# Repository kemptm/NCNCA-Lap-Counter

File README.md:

# NCNCA-Lap-Counter
This is an electronic lap counter for use at the finish line of bike (or other) races.  It has two 9" solenoid activated 7-segment digits. It is run by an Arduino controlled by a little remote control with buttons "A," "B," "C," and "D."   It has a solar panel to charge the batteries, but apparently can be powered by an external power supply. 

Mike's son built it as a college project.  There is no documentation.  It's not new, so some of the parts are obsolete.  If I can get it operational, Mike intends to donate it to the NCNCA.

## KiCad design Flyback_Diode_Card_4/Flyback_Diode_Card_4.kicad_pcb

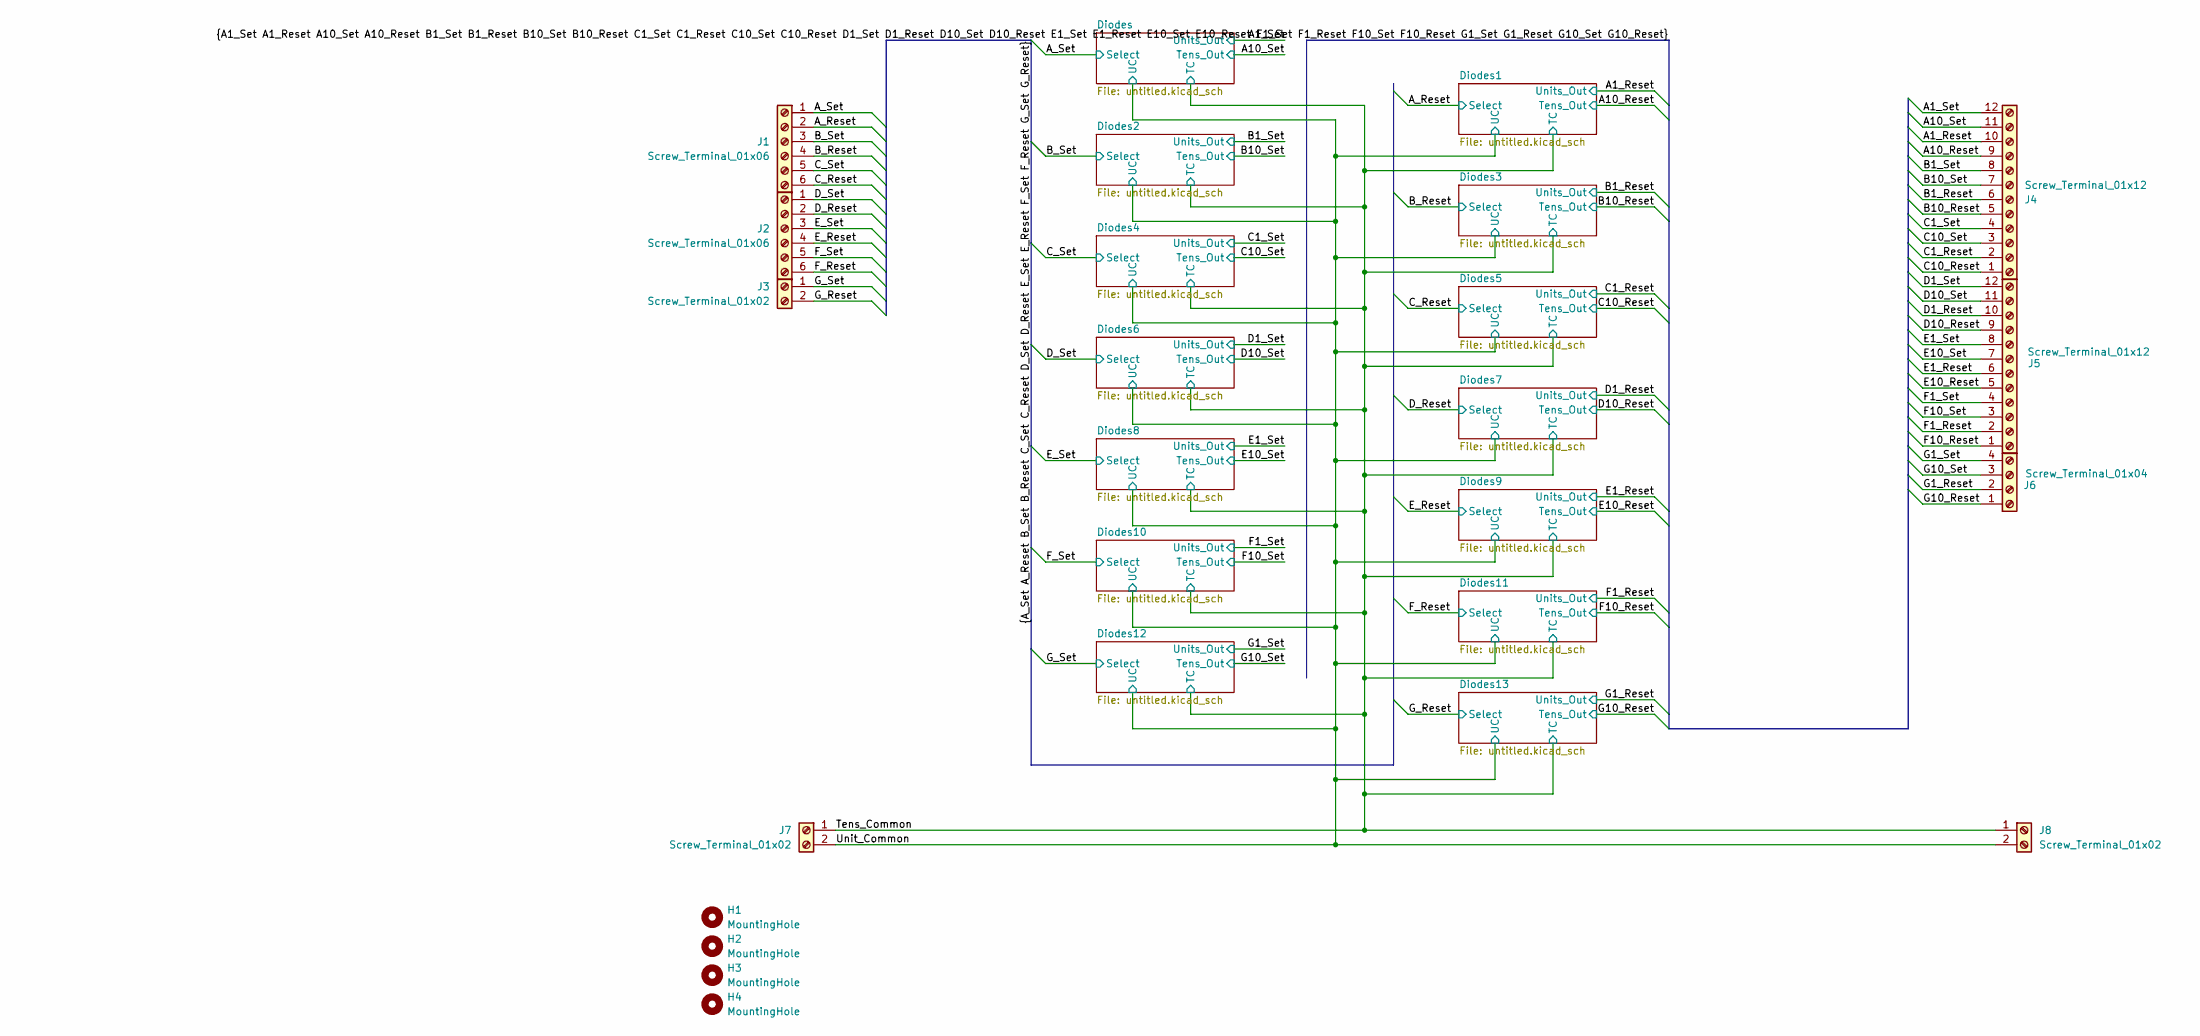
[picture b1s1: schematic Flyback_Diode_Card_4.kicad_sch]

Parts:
H1: MountingHole; MountingHole_3.2mm_M3_ISO7380
H2, H3, H4: MountingHole; MountingHole_3.2mm_M3_ISO14580
J1, J2: Screw_Terminal_01x06; TerminalBlock_Phoenix_MKDS-1,5-6-5.08_1x06_P5.08mm_Horizont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
J3, J7, J8: Screw_Terminal_01x02; TerminalBlock_Phoenix_MKDS-1,5-2-5.08_1x02_P5.08mm_Horizont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
J4, J5: Screw_Terminal_01x12; TerminalBlock_Phoenix_MPT-0,5-12-2.54_1x12_P2.54mm_Horizont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
J6: Screw_Terminal_01x04; TerminalBlock_Phoenix_MPT-0,5-4-2.54_1x04_P2.54mm_Horizontal

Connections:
/A1_Reset: J4.10; also elsewhere on the board
/A1_Set: J4.12; also elsewhere on the board
/A10_Reset: J4.9; also elsewhere on the board
/A10_Set: J4.11; also elsewhere on the board
/A_Reset: J1.2; also elsewhere on the board
/A_Set: J1.1; also elsewhere on the board
/B1_Reset: J4.6; also elsewhere on the board
/B1_Set: J4.8; also elsewhere on the board
/B10_Reset: J4.5; also elsewhere on the board
/B10_Set: J4.7; also elsewhere on the board
/B_Reset: J1.4; also elsewhere on the board
/B_Set: J1.3; also elsewhere on the board
/C1_Reset: J4.2; also elsewhere on the board
/C1_Set: J4.4; also elsewhere on the board
/C10_Reset: J4.1; also elsewhere on the board
/C10_Set: J4.3; also elsewhere on the board
/C_Reset: J1.6; also elsewhere on the board
/C_Set: J1.5; also elsewhere on the board
/D1_Reset: J5.10; also elsewhere on the board
/D1_Set: J5.12; also elsewhere on the board
/D10_Reset: J5.9; also elsewhere on the board
/D10_Set: J5.11; also elsewhere on the board
/D_Reset: J2.2; also elsewhere on the board
/D_Set: J2.1; also elsewhere on the board
/E1_Reset: J5.6; also elsewhere on the board
/E1_Set: J5.8; also elsewhere on the board
/E10_Reset: J5.5; also elsewhere on the board
/E10_Set: J5.7; also elsewhere on the board
/E_Reset: J2.4; also elsewhere on the board
/E_Set: J2.3; also elsewhere on the board
/F1_Reset: J5.2; also elsewhere on the board
/F1_Set: J5.4; also elsewhere on the board
/F10_Reset: J5.1; also elsewhere on the board
/F10_Set: J5.3; also elsewhere on the board
/F_Reset: J2.6; also elsewhere on the board
/F_Set: J2.5; also elsewhere on the board
/G1_Reset: J6.2; also elsewhere on the board
/G1_Set: J6.4; also elsewhere on the board
/G10_Reset: J6.1; also elsewhere on the board
/G10_Set: J6.3; also elsewhere on the board
/G_Reset: J3.2; also elsewhere on the board
/G_Set: J3.1; also elsewhere on the board
/Tens_Common: J7.1, J8.1; also elsewhere on the board
/Unit_Common: J7.2, J8.2; also elsewhere on the board

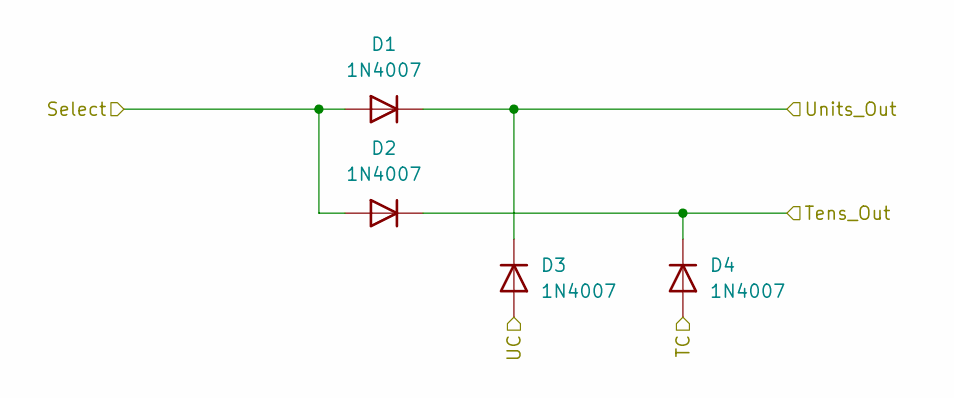
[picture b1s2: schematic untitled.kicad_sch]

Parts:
D1, D2, D3, D4: 1N4007; D_DO-41_SOD81_P10.16mm_Horizontal

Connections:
/A1_Reset: D1.1 (K), D3.1 (K); also elsewhere on the board
/A10_Reset: D2.1 (K), D4.1 (K); also elsewhere on the board
/A_Reset: D1.2 (A), D2.2 (A); also elsewhere on the board
/Tens_Common: D4.2 (A); also elsewhere on the board
/Unit_Common: D3.2 (A); also elsewhere on the board

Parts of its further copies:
D5, D6, D7, D8, D9, D10, D11, D12, D13, D14, D15, D16, D17, D18, D19, D20, D21, D22, D23, D24, D25, D26, D27, D28, D29, D30, D35, D36, D37, D38, D39, D40, D41, D42, D43, D44, D45, D46, D47, D48, D49, D50, D51, D52, D53, D54, D55, D56, D57, D58, D59, D60: 1N4007; D_DO-41_SOD81_P10.16mm_Horizontal

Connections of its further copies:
/A1_Set: D57.1 (K), D59.1 (K); also elsewhere on the board
/A10_Set: D58.1 (K), D60.1 (K); also elsewhere on the board
/A_Set: D57.2 (A), D58.2 (A); also elsewhere on the board
/B1_Reset: D9.1 (K), D11.1 (K); also elsewhere on the board
/B1_Set: D5.1 (K), D7.1 (K); also elsewhere on the board
/B10_Reset: D10.1 (K), D12.1 (K); also elsewhere on the board
/B10_Set: D6.1 (K), D8.1 (K); also elsewhere on the board
/B_Reset: D9.2 (A), D10.2 (A); also elsewhere on the board
/B_Set: D5.2 (A), D6.2 (A); also elsewhere on the board
/C1_Reset: D17.1 (K), D19.1 (K); also elsewhere on the board
/C1_Set: D13.1 (K), D15.1 (K); also elsewhere on the board
/C10_Reset: D18.1 (K), D20.1 (K); also elsewhere on the board
/C10_Set: D14.1 (K), D16.1 (K); also elsewhere on the board
/C_Reset: D17.2 (A), D18.2 (A); also elsewhere on the board
/C_Set: D13.2 (A), D14.2 (A); also elsewhere on the board
/D1_Reset: D25.1 (K), D27.1 (K); also elsewhere on the board
/D1_Set: D21.1 (K), D23.1 (K); also elsewhere on the board
/D10_Reset: D26.1 (K), D28.1 (K); also elsewhere on the board
/D10_Set: D22.1 (K), D24.1 (K); also elsewhere on the board
/D_Reset: D25.2 (A), D26.2 (A); also elsewhere on the board
/D_Set: D21.2 (A), D22.2 (A); also elsewhere on the board
/E1_Reset: D37.1 (K), D39.1 (K); also elsewhere on the board
/E1_Set: D29.1 (K), D35.1 (K); also elsewhere on the board
/E10_Reset: D38.1 (K), D40.1 (K); also elsewhere on the board
/E10_Set: D30.1 (K), D36.1 (K); also elsewhere on the board
/E_Reset: D37.2 (A), D38.2 (A); also elsewhere on the board
/E_Set: D29.2 (A), D30.2 (A); also elsewhere on the board
/F1_Reset: D45.1 (K), D47.1 (K); also elsewhere on the board
/F1_Set: D41.1 (K), D43.1 (K); also elsewhere on the board
/F10_Reset: D46.1 (K), D48.1 (K); also elsewhere on the board
/F10_Set: D42.1 (K), D44.1 (K); also elsewhere on the board
/F_Reset: D45.2 (A), D46.2 (A); also elsewhere on the board
/F_Set: D41.2 (A), D42.2 (A); also elsewhere on the board
/G1_Reset: D53.1 (K), D55.1 (K); also elsewhere on the board
/G1_Set: D49.1 (K), D51.1 (K); also elsewhere on the board
/G10_Reset: D54.1 (K), D56.1 (K); also elsewhere on the board
/G10_Set: D50.1 (K), D52.1 (K); also elsewhere on the board
/G_Reset: D53.2 (A), D54.2 (A); also elsewhere on the board
/G_Set: D49.2 (A), D50.2 (A); also elsewhere on the board
/Tens_Common: D8.2 (A), D12.2 (A), D16.2 (A), D20.2 (A), D24.2 (A), D28.2 (A), D36.2 (A), D40.2 (A), D44.2 (A), D48.2 (A), D52.2 (A), D56.2 (A), D60.2 (A); also elsewhere on the board
/Unit_Common: D7.2 (A), D11.2 (A), D15.2 (A), D19.2 (A), D23.2 (A), D27.2 (A), D35.2 (A), D39.2 (A), D43.2 (A), D47.2 (A), D51.2 (A), D55.2 (A), D59.2 (A); also elsewhere on the board

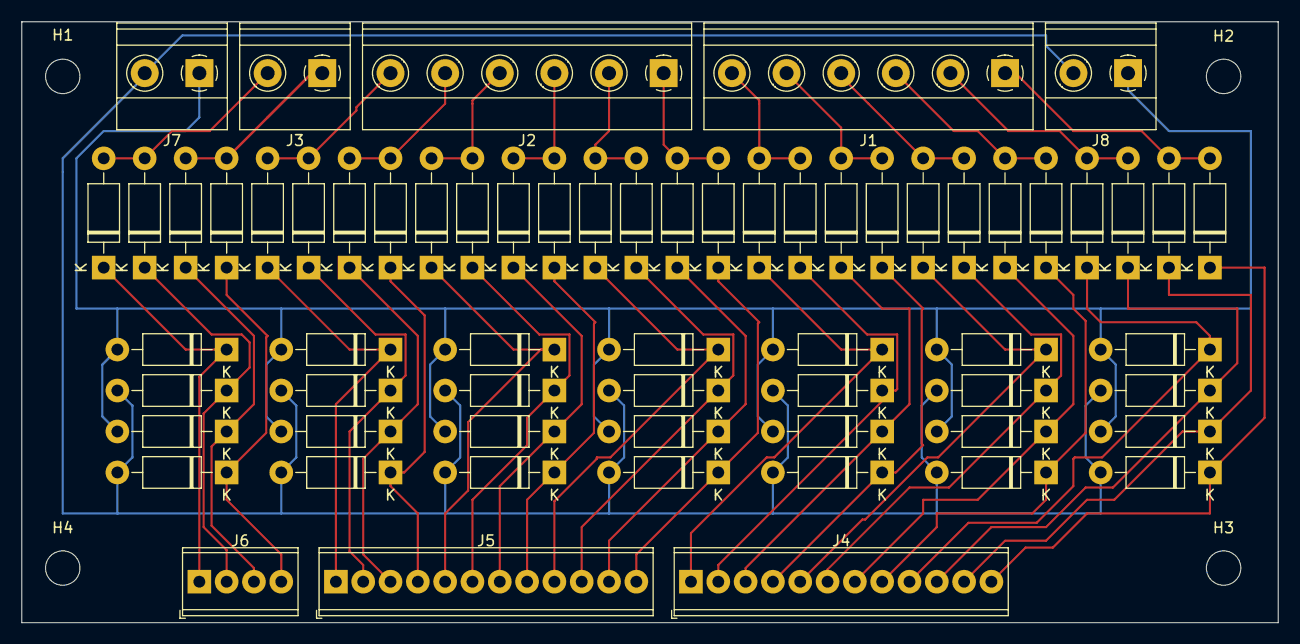
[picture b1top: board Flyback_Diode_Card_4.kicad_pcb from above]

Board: 2 copper layers, 116.8 x 55.9 mm, 68 parts (0 on the bottom side), 44 nets.

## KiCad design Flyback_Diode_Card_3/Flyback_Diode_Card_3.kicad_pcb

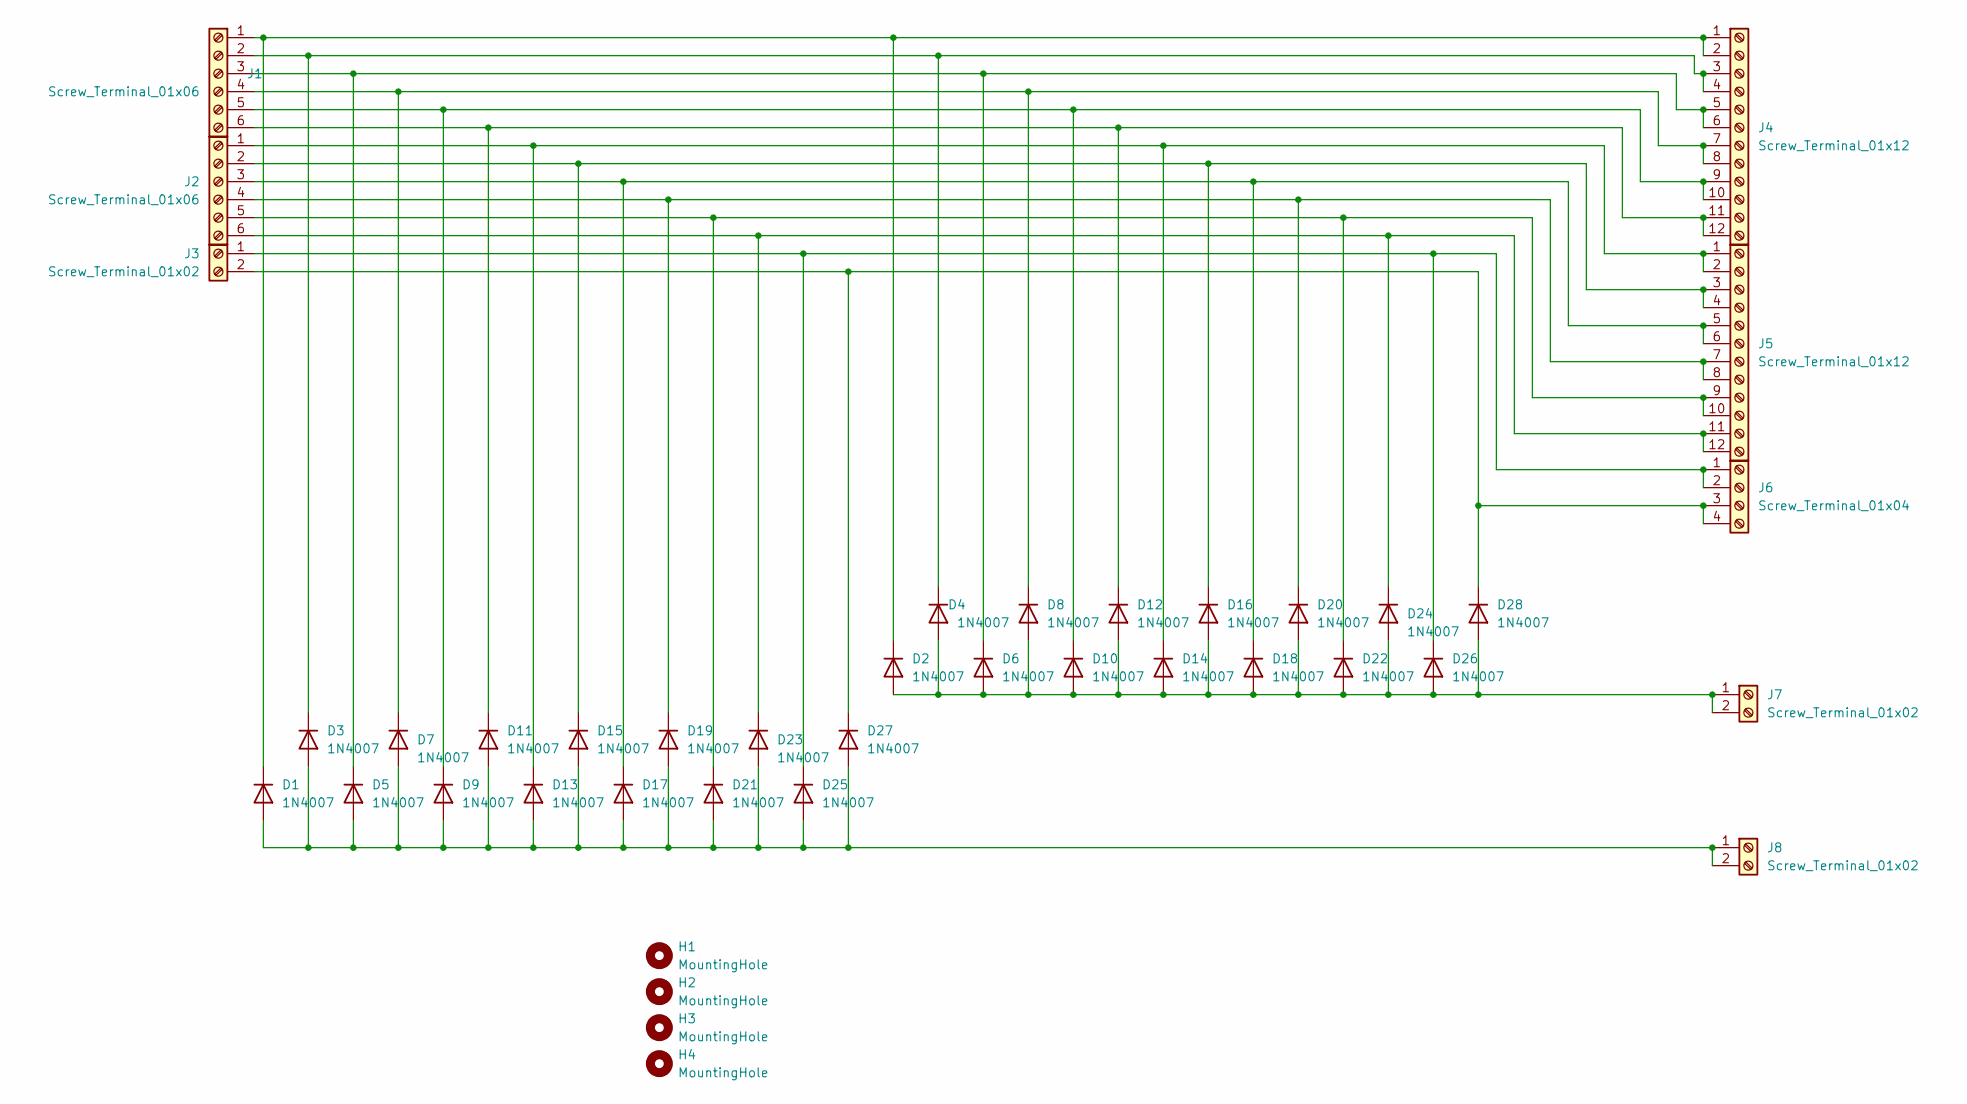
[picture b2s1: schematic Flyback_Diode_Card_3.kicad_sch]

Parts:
D1, D2, D3, D4, D5, D6, D7, D8, D9, D10, D11, D12, D13, D14, D15, D16, D17, D18, D19, D20, D21, D22, D23, D24, D25, D26, D27, D28: 1N4007; D_DO-41_SOD81_P10.16mm_Horizontal
H1: MountingHole; MountingHole_3.2mm_M3_ISO7380
H2, H3, H4: MountingHole; MountingHole_3.2mm_M3_ISO14580
J1, J2: Screw_Terminal_01x06; PhoenixContact_MCV_1,5_6-G-5.08_1x06_P5.08mm_Vertical
J3: Screw_Terminal_01x02; PhoenixContact_MCV_1,5_2-G-5.08_1x02_P5.08mm_Vertical
J4, J5: Screw_Terminal_01x12; TerminalBlock_Phoenix_MPT-0,5-12-2.54_1x12_P2.54mm_Horizont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
J6: Screw_Terminal_01x04; TerminalBlock_Phoenix_MPT-0,5-4-2.54_1x04_P2.54mm_Horizontal
J7, J8: Screw_Terminal_01x02; TerminalBlock_Phoenix_MKDS-3-2-5.08_1x02_P5.08mm_Horizontal

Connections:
unnamed: D1.2 (A), D3.2 (A), D5.2 (A), D7.2 (A), D9.2 (A), D11.2 (A), D13.2 (A), D15.2 (A), D17.2 (A), D19.2 (A), D21.2 (A), D23.2 (A), D25.2 (A), D27.2 (A), J8.1, J8.2
unnamed: D1.1 (K), D2.1 (K), J1.1, J4.1, J4.2
unnamed: D3.1 (K), D4.1 (K), J1.2, J4.3, J4.4
unnamed: D5.1 (K), D6.1 (K), J1.3, J4.5, J4.6
unnamed: D7.1 (K), D8.1 (K), J1.4, J4.7, J4.8
unnamed: D2.2 (A), D4.2 (A), D6.2 (A), D8.2 (A), D10.2 (A), D12.2 (A), D14.2 (A), D16.2 (A), D18.2 (A), D20.2 (A), D22.2 (A), D24.2 (A), D26.2 (A), D28.2 (A), J7.1, J7.2
unnamed: D9.1 (K), D10.1 (K), J1.5, J4.9, J4.10
unnamed: D11.1 (K), D12.1 (K), J1.6, J4.11, J4.12
unnamed: D13.1 (K), D14.1 (K), J2.1, J5.1, J5.2
unnamed: D15.1 (K), D16.1 (K), J2.2, J5.3, J5.4
unnamed: D17.1 (K), D18.1 (K), J2.3, J5.5, J5.6
unnamed: D19.1 (K), D20.1 (K), J2.4, J5.7, J5.8
unnamed: D21.1 (K), D22.1 (K), J2.5, J5.9, J5.10
unnamed: D23.1 (K), D24.1 (K), J2.6, J5.11, J5.12
unnamed: D25.1 (K), D26.1 (K), J3.1, J6.1, J6.2
unnamed: D27.1 (K), D28.1 (K), J3.2, J6.3, J6.4

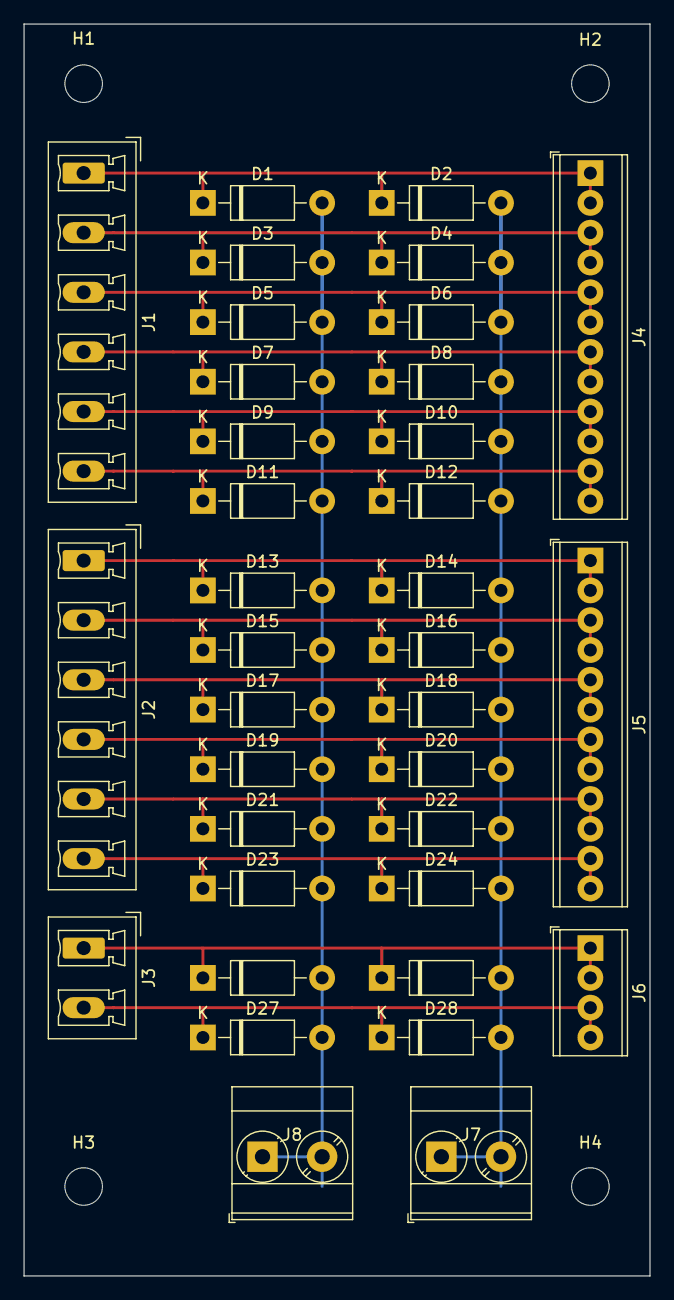
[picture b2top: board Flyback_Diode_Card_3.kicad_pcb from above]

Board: 2 copper layers, 53.3 x 106.7 mm, 40 parts (0 on the bottom side), 16 nets.

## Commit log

2023-08-30 Lap Counter Hardware and Software for the NCNCA
    Hardware and Software descriptions
2023-08-30 Add Documents
    Collected documentation (such as it is) from parts descriptions of the components. Also some images of the counter itself.
2023-08-30 Update README.md
    Background and description of project
2023-08-30 Update README.md
    Update formatting
2023-08-30 Pictures and Symbols added
    Added symbols for two components
2023-09-02 Docs and symbols
    Added documentation of items similar to those in the counter. I also defined symbols for them.
2023-09-03 More docs & new schematic
    Found Arduino schematics and built power supply schematic
2023-09-06 Rearrange documentation
2023-09-24 Schematic in state of received unit. Will branch from here.
2023-10-29 Documentation and mechanical drawings added along with change to matrix relay definition
2023-10-29 schematic and pcb changes
2023-11-13 Add mechanical drawings
2023-11-13 changes to mechanical drawings
2024-01-13 lots of diagram changes and software dir.
2024-02-01 Misc clean up
2024-02-01 Get everything into sync
2024-02-04 First complete implementation of Lap Counter run time.
2024-02-09 bug fixes from desk check and documentation
2024-02-16 Document the source code with Doxygen
2024-02-16 Document using Atomineer and Doxygen
2024-02-16 Omit documentation
2024-02-16 Make sure that the documentation makes it.
2024-02-20 Bring external projects under this umbrella
2024-03-06 Include mechanical and electrical physical drawings
2024-03-27 Documentation clean up and addition of spec sheets
2024-04-03 Update deverlopment log
2024-04-12 Add support for local membrane keyboard and update main loop to use new implementation for both membrane and radio keyboards.
2024-04-12 Try to clean up include path (failed)
2024-04-12 Correct images inclusion in Development log
2024-04-15 First working version. It responds to putton presses by firing the solenoids. Not completely tested yet, though.
2024-04-19 Update development log and physical layout drawing.
2024-04-19 Include photos and FreeCAD drawing
2024-04-19 Missed a photo for log
2024-04-21 All electronics mounted!
2024-05-01 First functioning version; at least as far as POST
2024-05-01 Update documentation
2024-05-08 Review of why Flyback Diocde Card 3 didn't work and initial design of Flyback Diode Card 4. Commentary in the development log.
2024-05-09 Working on new flyback diode card/
2024-05-09 Finished and submitted for manufacturing New PCB Flyback Board
2024-05-09 Add KiCAD output files to .gitignore
2024-05-10 Add picture of breadboard test.
2024-05-12 clean up messy bus connections to flyback card and produce a new print schematic.
2024-05-24 Made it work. I also made the segment solenoid current hold time specifiable by segment. Some of the segments are slow and got unreliable with short pulses.
2024-05-24 This is a test program. Note that there are copies of the include files. Unfortunately a requirement of the Arduino compiler. These may or may not represent the code in the LapCounter directory and s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
2024-05-25 eliminate over-large mp4 file
2024-05-26 Put on back panel, test it and note it in the log.
2024-06-07 Documentation Updates
2024-06-07 Up to date on the Blog
2024-06-07 Version 1.0
2024-06-13 Configure pins for new radio.
2024-06-13 Update documen
2024-06-17 Last of signal cables installed
2024-07-01 Final solenoid timings for first outing
2024-07-01 Update Documentation for added regulator.
